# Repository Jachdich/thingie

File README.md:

# thingie

the "thingie" is a multi-purpose microcontroller-based portable device that does... things. current plan is to make it play simple games, be an MP3 player, and be able to run some kind of programming interface. It can and will be extended to do cool and/or stupid and/or useless things in the future. This repo contains the PCB design, which is the most scuffed thing in the world as it uses components that don't exist and you have to make yourself by frankensteining a bunch of buttons together. Maybe one day if it works I will make a proper documentation of how to build one but right now it does not work (or even exist) so I don't see the point.

uses kicad 7

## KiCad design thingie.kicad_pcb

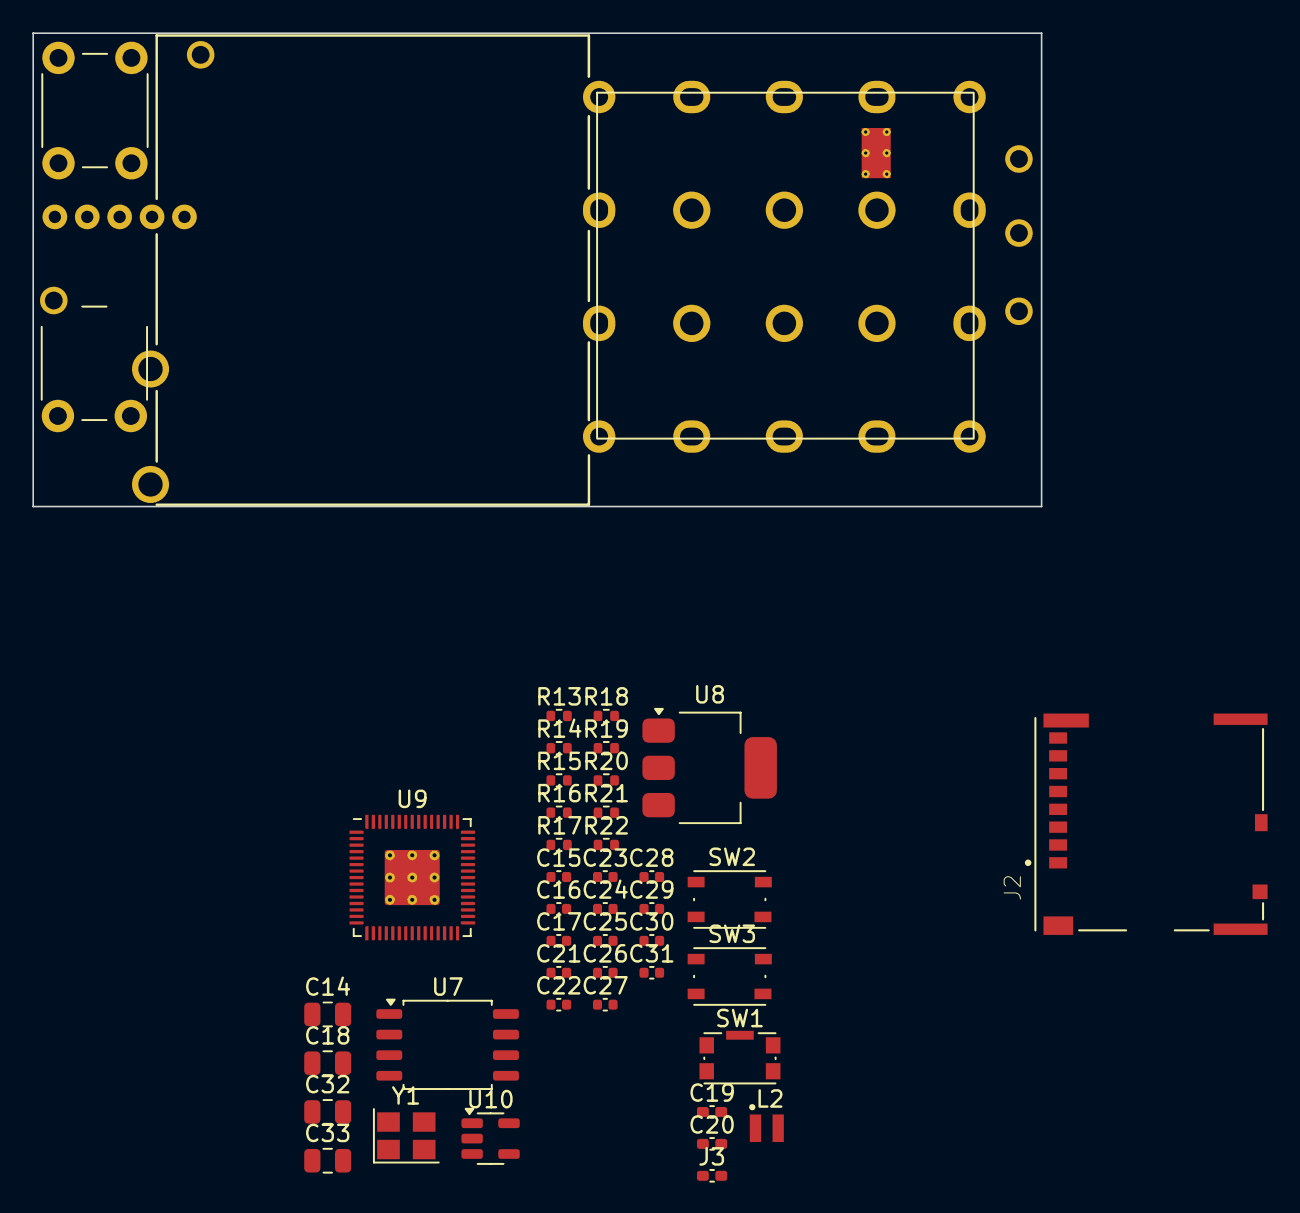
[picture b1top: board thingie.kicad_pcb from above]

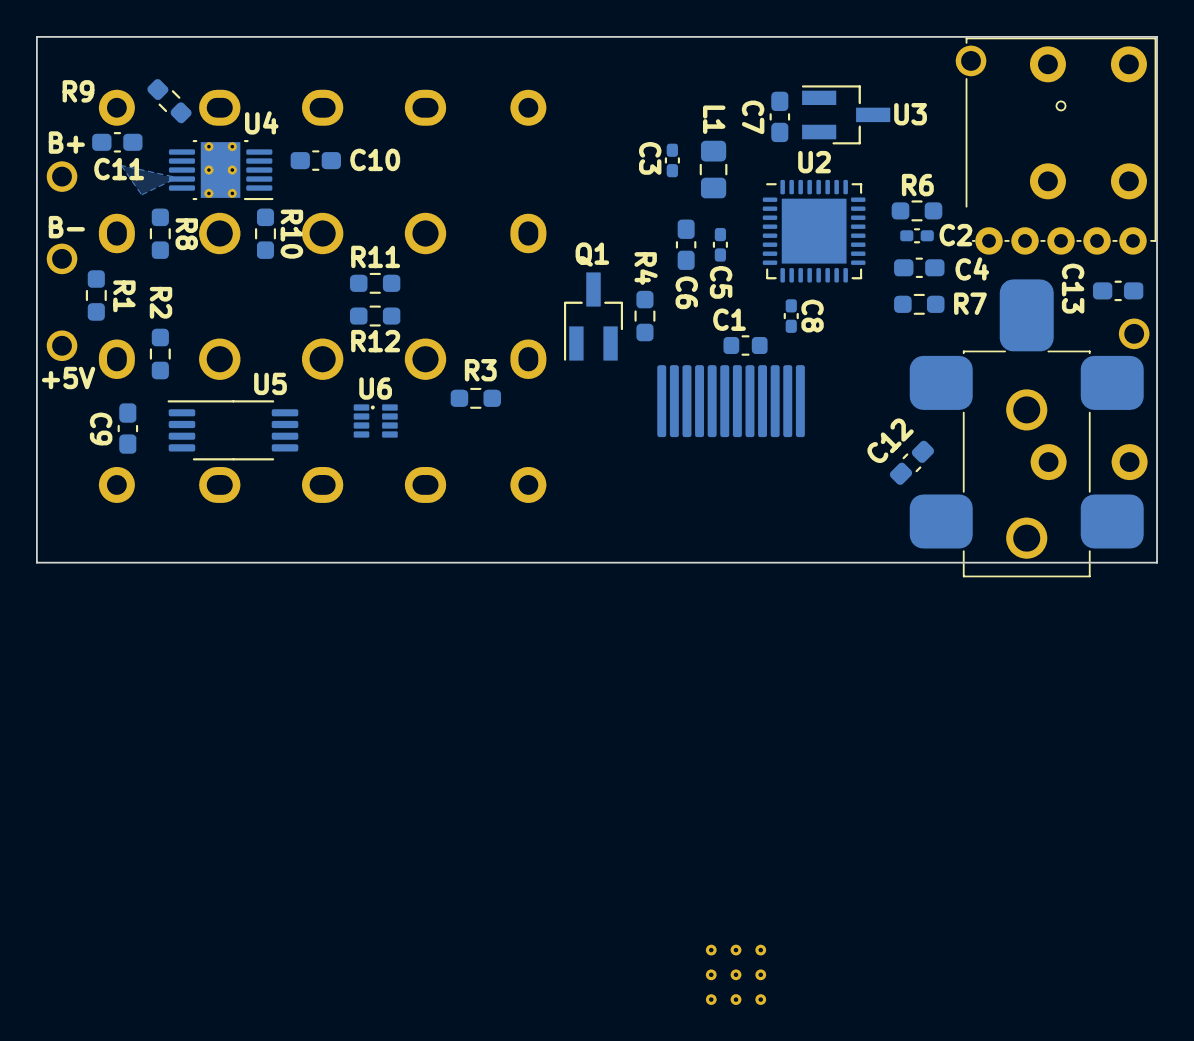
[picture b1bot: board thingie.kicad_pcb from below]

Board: 4 copper layers, 62.2 x 29.2 mm, 82 parts (34 on the bottom side), 49 nets, no tracks yet.

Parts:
C1: C; C_0603_1608Metric
C2, C3, C5: 0.1µF; C_0402_1005Metric_Pad0.74x0.62mm_HandSolder
C4, C6, C7: 2.2µF; C_0603_1608Metric_Pad1.08x0.95mm_HandSolder
C8: 0.15µF; C_0402_1005Metric_Pad0.74x0.62mm_HandSolder
C9, C10: 0.1µF; C_0603_1608Metric_Pad1.08x0.95mm_HandSolder
C11: 4.7µF; C_0603_1608Metric_Pad1.08x0.95mm_HandSolder
C12, C13: 10µF; C_0603_1608Metric_Pad1.08x0.95mm_HandSolder
C14, C18, C32, C33: 10u; C_0805_2012Metric
C15, C16: 15p; C_0402_1005Metric
C17, C21, C24, C25, C26, C27, C28, C29, C30, C31: 100n; C_0402_1005Metric
C19, C20: 4.7u; C_0402_1005Metric_Pad0.74x0.62mm_HandSolder
C22, C23: 4.7u; C_0402_1005Metric
J2: Micro_SD_Card_Det; SDCARD_MOLEX_503398-1892
J3: USB_C_Receptacle_USB2.0_14P; C_0402_1005Metric_Pad0.74x0.62mm_HandSolder
J3#2, J10, J37, J38: Conn_01x01_Male; hole
J8: Conn_01x12; SMD_CON_1x11_0.7mm
J36: AudioJack4; audio_3.5mm_trrs
L1: ferrite 600; L_0805_2012Metric_Pad1.15x1.40mm_HandSolder
L2: 3.3u; L_pol_2016
Q1: Q_NPN_BEC; SOT-23_Handsoldering
R1: 20mR; R_0603_1608Metric_Pad0.98x0.95mm_HandSolder
R2: 500R; R_0603_1608Metric_Pad0.98x0.95mm_HandSolder
R3: 10K; R_0603_1608Metric_Pad0.98x0.95mm_HandSolder
R4: 10R; R_0603_1608Metric_Pad0.98x0.95mm_HandSolder
R5: thumbwheel_pot
R6: 100R; R_0603_1608Metric_Pad0.98x0.95mm_HandSolder
R7: 270R; R_0603_1608Metric_Pad0.98x0.95mm_HandSolder
R8: 1K; R_0603_1608Metric_Pad0.98x0.95mm_HandSolder
R9: 1K87; R_0603_1608Metric_Pad0.98x0.95mm_HandSolder
R10: 400K; R_0603_1608Metric_Pad0.98x0.95mm_HandSolder
R11: 2K2; R_0603_1608Metric_Pad0.98x0.95mm_HandSolder
R12: 820R; R_0603_1608Metric_Pad0.98x0.95mm_HandSolder
R13, R15: DNF; R_0402_1005Metric
R14: 0; R_0402_1005Metric
R16, R17, R19: 1k; R_0402_1005Metric
R18: 33; R_0402_1005Metric
R20, R21: 27; R_0402_1005Metric
R22: 12K 1%; R_0402_1005Metric
SW1: SW_SPST; SW_Push_1P1T-SH_NO_CK_KMR2xxG
SW2, SW3: SW_Push; SW_Push_1P1T_NO_Vertical_Wuerth_434133025816
SW13, SW14: SW_Push; SW_PUSH_6mm_H5mm
U1: buttonarray; button_array
U2: SGTL5000XNAA3; QFN-32-1EP_5x5mm_P0.5mm_EP3.6x3.6mm
U3: AP7313; SOT-23_Handsoldering
U4: LTC1733; MSOP-10-1EP_3x3mm_P0.5mm_EP2.2x3.1mm_Mask1.83x1.89mm_Therma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
U5: DS2782; TSSOP-8_4.4x3mm_P0.65mm
U6: TPS2116; SOT-5X3
U7: W25Q128JVS; SOIC-8_5.23x5.23mm_P1.27mm
U8: NCP1117-3.3_SOT223; SOT-223-3_TabPin2
U9: RP2350_60QFN; RP2350-QFN-60-1EP_7x7_P0.4mm_EP3.4x3.4mm_ThermalVias
U10: RT9742GGJ5; SOT-23-5
Y1: ABM8-272-T3; Crystal_SMD_3225-4Pin_3.2x2.5mm

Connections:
+1V1: C20.1, C21.1, C23.1, C24.1, L2.1, U9.6 (DVDD), U9.23 (DVDD), U9.39 (DVDD), U9.50 (VREG_FB)
+3V3: C1.2, C2.1, C3.1, C4.1, C17.1, C18.1, C19.1, C25.1, C26.1, C27.1, C28.1, C29.1, C30.1, C31.1, C32.1, J8.9, J8.10, L1.1, R5.3, R7.1, R15.1, R18.1, U2.20 (VDDIO), U3.1 (Vin), U7.8 (VCC), U8.2 (VO), U9.1 (IOVDD), U9.11 (IOVDD), U9.20 (IOVDD), U9.30 (IOVDD), U9.38 (IOVDD), U9.44 (ADC_AVDD), U9.45 (IOVDD), U9.49 (VREG_VIN), U9.53 (USB_OTP_VDD), U9.54 (QSPI_IOVDD)
+5V: C11.1, J38.1, R10.2, R11.1, U4.2 (Vcc), U4.8 (SEL), U6.3 (Vin1), U6.5 (MODE)
+BATT: J10.1, R2.1, R8.1, U4.9 (BAT), U6.6 (Vin2)
/+1V8: C7.1, U2.30 (VDDD), U3.2 (Vout)
/+3.3v: R22.1, U10.5 (IN)
/AUDIO_GND: J36.R2, U2.4 (HP_VGND)
/BUTTON_SENSE: J36.S, R7.2
/CELL-: C9.1, J37.1, R1.1, U5.2 (VSS)
/CHG_ON: R10.1, U4.1 (/CHRG)
/FLASH_SS: R13.2, R14.2, R15.2, U7.1 (~CS)
/LCD_BL: J8.11, R4.1
/LEFT: J36.T, U2.6 (HP_L)
/QSPI_SCLK: U7.6 (CLK), U9.56 (QSPI_SCLK)
/QSPI_SD0: U7.5 (DI(IO0)), U9.57 (QSPI_SD0)
/QSPI_SD1: U7.2 (DO(IO1)), U9.59 (QSPI_SD1)
/QSPI_SD2: U7.3 (IO2), U9.58 (QSPI_SD2)
/QSPI_SD3: U7.7 (IO3), U9.55 (QSPI_SD3)
/QSPI_SS: R14.1, R19.1, U9.60 (QSPI_SS)
/RIGHT: J36.R1, U2.2 (HP_R)
/RUN: SW3.2, U9.26 (RUN)
/SCL: U2.29 (CTRL_CLK), U5.6 (SCL)
/SDA: U2.27 (CTRL_DATA), U5.5 (SDA)
/SD_PWR: C33.1, J2.4 (VDD), U10.1 (OUT)
/SD_PWR_ON: R22.2, U10.4 (EN)
/VREG_AVDD: C22.1, R18.2, U9.46 (VREG_AVDD)
/VREG_LX: L2.2, U9.48 (VREG_LX)
/XIN: C15.1, U9.21 (XIN), Y1.1
/XOUT: R16.1, U9.22 (XOUT)
/~USB_BOOT: R19.2, SW2.2
GND: Y1.2, Y1.4
GND1: C10.2, C11.2, R1.2, R9.2, SW1.1 (A), U4.5 (GND), U4.6 (NTC), U5.7 (SNS)
GNDREF: C1.1, C2.2, C3.2, C4.2, C5.2, C6.2, C7.2, C8.1, C12.2, C13.2, C14.2, C15.2, C16.2, C17.2, C18.2, C19.2, C20.2, C21.2, C22.2, C23.2, C24.2, C25.2, C26.2, C27.2, C28.2, C29.2, C30.2, C31.2, C32.2, C33.2, J2.6 (VSS), J2.11 (SHIELD), J8.1, J8.7, J8.8, J8.12, Q1.2 (E), R5.1, R12.2, R17.2, SW1.2 (B), SW2.1, SW13.2, SW14.2, U1.13 (GND), U2.1 (GND), U2.3 (GND), U2.7 (AGND), U2.13 (LINEIN_R), U2.14 (LINEIN_L), U2.15 (MIC), U2.31 (CTRL_ADR0_CS), U2.32 (CTRL_MODE), U2.33 (GND), U3.3 (GND), U6.1 (GND), U8.1 (GND), U9.47 (VREG_PGND), U9.61 (GND), U10.2 (GND)
unnamed: C16.1, R16.2, Y1.3
unnamed: Q1.1 (B), R3.2
unnamed: Q1.3 (C), R4.2
unnamed: R17.1, SW3.1
unnamed: R6.2, U2.21 (SYS_MCLK)
unnamed: C8.2, U2.10 (VAG)
unnamed: C5.1, C6.1, L1.2, U2.5 (VDDA)
unnamed: R9.1, U4.7 (PROG)
unnamed: C10.1, U4.4 (TIMER)
unnamed: C9.2, R2.2, U5.4 (VDD)
unnamed: R8.2, U5.3 (VIN)
unnamed: R11.2, R12.1, U6.4 (PR1)
unnamed: R21.2, U9.51 (USB_DM)
unnamed: R20.2, U9.52 (USB_DP)
VBUS: C14.1, U8.3 (VI)
VCC: C12.1, C13.1, J3#2.1, U6.7 (Vout)

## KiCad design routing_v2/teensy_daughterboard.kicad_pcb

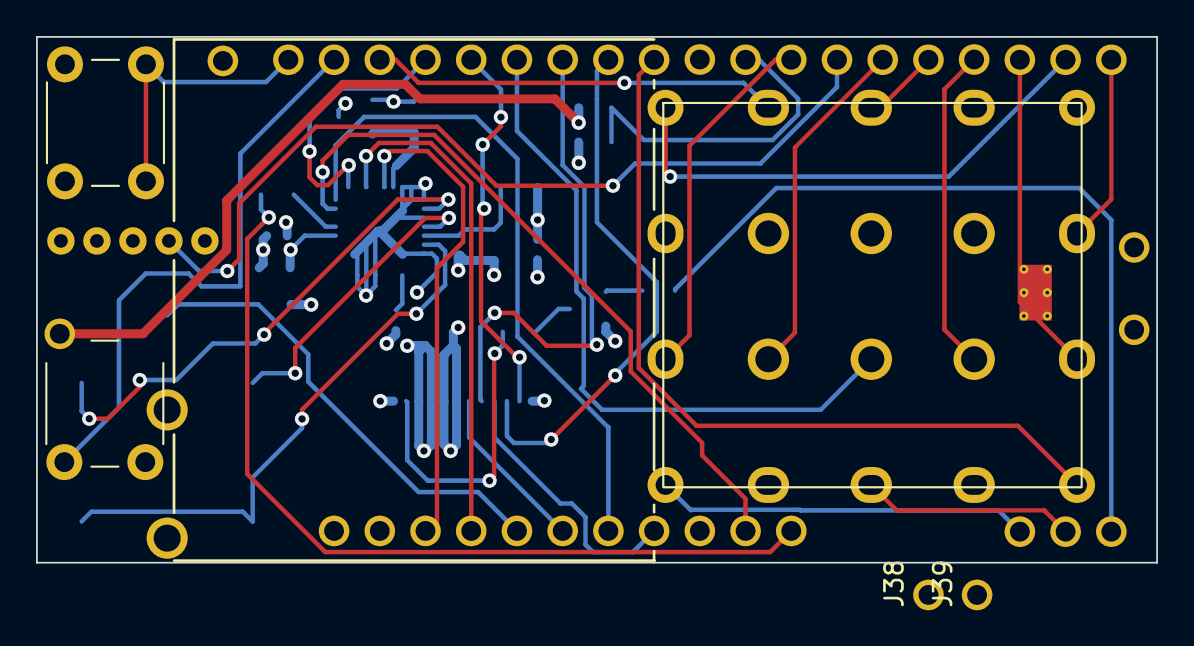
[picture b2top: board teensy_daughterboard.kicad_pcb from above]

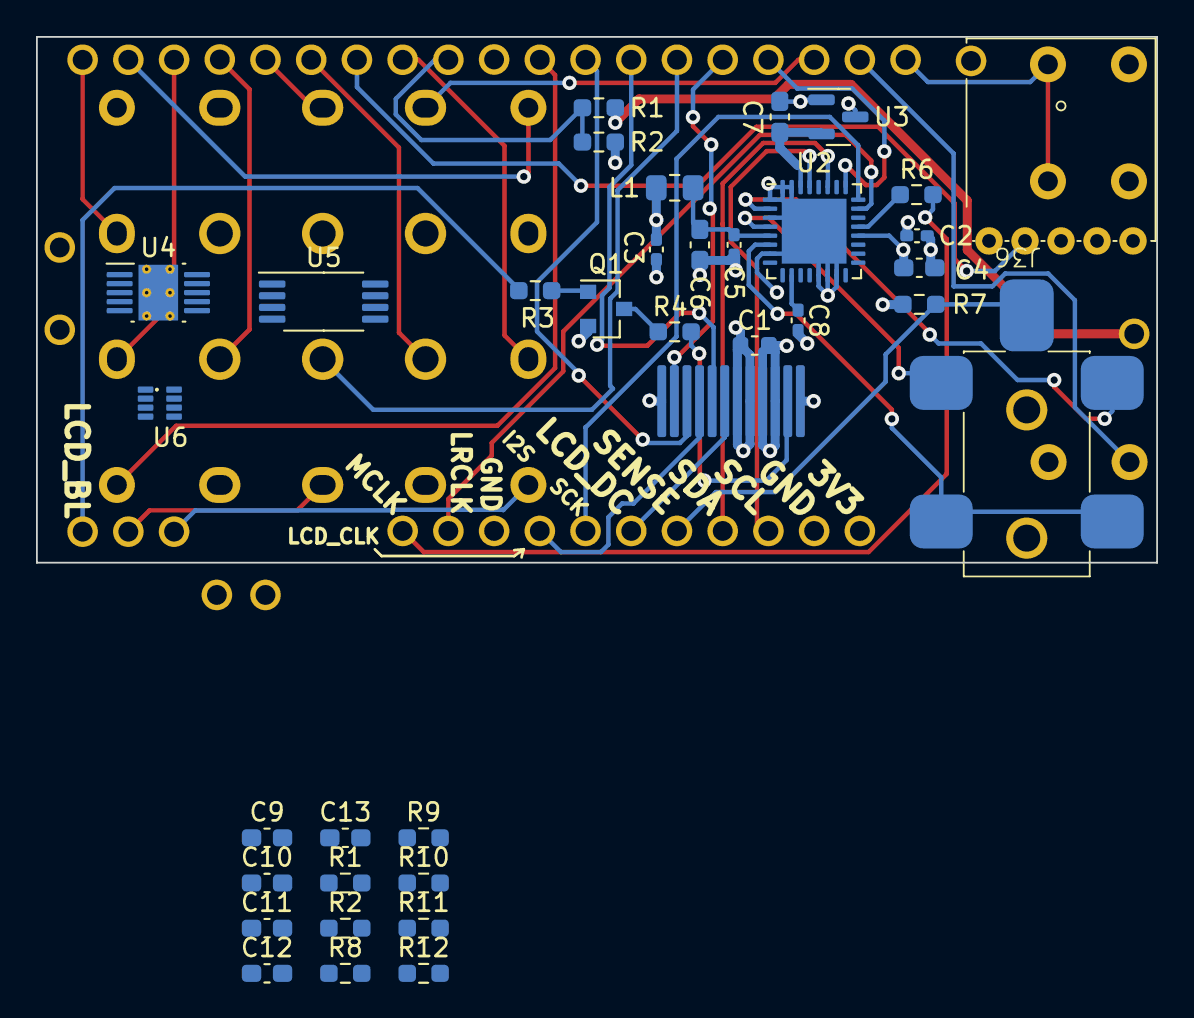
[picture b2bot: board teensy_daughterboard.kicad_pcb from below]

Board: 4 copper layers, 62.2 x 29.2 mm, 77 parts (36 on the bottom side), 52 nets.

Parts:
C1: C; C_0603_1608Metric
C2, C3, C5: 0.1µF; C_0402_1005Metric_Pad0.74x0.62mm_HandSolder
C4, C6, C7: 2.2µF; C_0603_1608Metric_Pad1.08x0.95mm_HandSolder
C8: 0.15µF; C_0402_1005Metric_Pad0.74x0.62mm_HandSolder
C9, C10: 0.1µF; C_0603_1608Metric_Pad1.08x0.95mm_HandSolder
C11: 4.7µF; C_0603_1608Metric_Pad1.08x0.95mm_HandSolder
C12, C13: 10µF; C_0603_1608Metric_Pad1.08x0.95mm_HandSolder
J1, J2, J3, J4, J5, J6, J7, J9, J10, J10#2, J11, J12, J13, J14, J15, J16, J17, J18, J19, J20, J21, J22, J23, J24, J25, J26, J27, J28, J29, J30, J31, J32, J33, J34, J35, J37, J38, J39: Conn_01x01_Male; hole
J8: Conn_01x12; SMD_CON_1x11_0.7mm
J36: AudioJack4; audio_3.5mm_trrs
L1: ferrite 600; L_0805_2012Metric_Pad1.15x1.40mm_HandSolder
Q1: Q_NPN_BEC; SOT-23
R1: 20mR; R_0603_1608Metric_Pad0.98x0.95mm_HandSolder
R1#2, R2#2: R; R_0603_1608Metric_Pad0.98x0.95mm_HandSolder
R2: 500R; R_0603_1608Metric_Pad0.98x0.95mm_HandSolder
R3: 10K; R_0603_1608Metric_Pad0.98x0.95mm_HandSolder
R4: 10R; R_0603_1608Metric_Pad0.98x0.95mm_HandSolder
R5: thumbwheel_pot
R6: 100R; R_0603_1608Metric_Pad0.98x0.95mm_HandSolder
R7: 270R; R_0603_1608Metric_Pad0.98x0.95mm_HandSolder
R8: 1K; R_0603_1608Metric_Pad0.98x0.95mm_HandSolder
R9: 1K87; R_0603_1608Metric_Pad0.98x0.95mm_HandSolder
R10: 400K; R_0603_1608Metric_Pad0.98x0.95mm_HandSolder
R11: 2K2; R_0603_1608Metric_Pad0.98x0.95mm_HandSolder
R12: 820R; R_0603_1608Metric_Pad0.98x0.95mm_HandSolder
SW13, SW14: SW_Push; SW_PUSH_6mm_H5mm
U1: buttonarray; button_array
U2: SGTL5000XNAA3; QFN-32-1EP_5x5mm_P0.5mm_EP3.6x3.6mm
U3: SOT-23
U4: LTC1733; MSOP-10-1EP_3x3mm_P0.5mm_EP2.2x3.1mm_Mask1.83x1.89mm_Therma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
U5: DS2782; TSSOP-8_4.4x3mm_P0.65mm
U6: TPS2116; SOT-5X3

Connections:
+3V3: C1.2, C2.1, C3.1, C4.1, J4.1, J5.1, J8.9, J8.10, L1.1, R5.3, R7.1, U2.20 (VDDIO), U3.1 (Vin)
+5V: C11.1, J38.1, R10.2, R11.1, U4.2 (Vcc), U4.8 (SEL), U6.3 (Vin1), U6.5 (MODE)
+BATT: J10#2.1, R2.1, R8.1, U4.9 (BAT), U6.6 (Vin2)
/+1V8: C7.1, U2.30 (VDDD), U3.2 (Vout)
/AUDIO_GND: J36.R2, U2.4 (HP_VGND)
/BUTTON_SENSE: J11.1, J36.S, R7.2
/CELL-: C9.1, J37.1, R1.1, U5.2 (VSS)
/I2S_DATA: J32.1, U2.26 (I2S_DIN)
/I2S_LRCLK: J34.1, U2.23 (I2S_LRCLK)
/I2S_MCLK: J35.1, R6.1
/I2S_SCLK: J33.1, U2.24 (I2S_SCLK)
/LCD_BL: J8.11, R4.1
/LCD_BL_CONT: J2.1, R3.1
/LCD_CLK: J8.4, J29.1
/LCD_CS: J8.5, J28.1
/LCD_DC: J8.6, J27.1
/LCD_DIN: J8.3, J30.1
/LCD_RST: J8.2, J31.1
/LEFT: J36.T, U2.6 (HP_L)
/PWR_SRC: J39.1, U6.8 (ST)
/RIGHT: J36.R1, U2.2 (HP_R)
/SCL: J25.1, U2.29 (CTRL_CLK), U5.6 (SCL)
/SDA: J26.1, U2.27 (CTRL_DATA), U5.5 (SDA)
/VOLT_MEASURE: J10.1, R1#2.2, R2#2.1
/vol_pot_measure: J7.1, R5.2
GNDREF: C1.1, C2.2, C3.2, C4.2, C5.2, C6.2, C7.2, C8.1, C10.2, C11.2, C12.2, C13.2, J6.1, J8.1, J8.7, J8.8, J8.12, J9.1, Q1.2 (E), R1.2, R2#2.2, R5.1, R9.2, R12.2, SW13.1, SW14.1, U1.13 (GND), U2.1 (GND), U2.3 (GND), U2.7 (AGND), U2.13 (LINEIN_R), U2.14 (LINEIN_L), U2.15 (MIC), U2.31 (CTRL_ADR0_CS), U2.32 (CTRL_MODE), U2.33 (GND), U3.3 (GND), U4.5 (GND), U4.6 (NTC), U5.7 (SNS), U6.1 (GND)
unnamed: J1.1, SW13.2
unnamed: J12.1, SW14.2
unnamed: J13.1, U1.12
unnamed: J14.1, U1.11
unnamed: J15.1, U1.10
unnamed: J16.1, U1.9
unnamed: J17.1, U1.7
unnamed: J18.1, U1.8
unnamed: J19.1, U1.6
unnamed: J20.1, U1.5
unnamed: J21.1, U1.4
unnamed: J22.1, U1.3
unnamed: J23.1, U1.2
unnamed: J24.1, U1.1
unnamed: Q1.1 (B), R3.2
unnamed: Q1.3 (C), R4.2
unnamed: R6.2, U2.21 (SYS_MCLK)
unnamed: C8.2, U2.10 (VAG)
unnamed: C5.1, C6.1, L1.2, U2.5 (VDDA)
unnamed: R9.1, U4.7 (PROG)
unnamed: C10.1, U4.4 (TIMER)
unnamed: R10.1, U4.1 (/CHRG)
unnamed: C9.2, R2.2, U5.4 (VDD)
unnamed: R8.2, U5.3 (VIN)
unnamed: R11.2, R12.1, U6.4 (PR1)
VCC: C12.1, C13.1, J3.1, R1#2.1, U6.7 (Vout)

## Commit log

2024-09-27 remove unnecessary files
2024-09-27 start modifying the schematic in preperation to add an RP2350
2024-09-27 shittiest readme ever
2024-09-29 new µc schematic - it ain't all fitting on the PCB. Hmph.
